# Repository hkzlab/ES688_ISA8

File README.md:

# ES688F / OPL3 8bit ISA Sound Card

## Introduction

This is a sound card for the ISA 8bit bus sporting the **ES688F** chip by *ESS Technology* and the **YMF262** chip by *Yamaha*, also known as the **OPL3**.

This board provides selectable **Sound Blaster PRO** / **Sound Blaster** emulation and **OPL3** compatibility.

It's completely jumper-configurable, requiring no software except the *essvol* utility to set the volume.

This board provides the following connections:

* Speaker out (amplified)
* Line out
* Line in
* Aux in (internal header)
* Microphone in (internal header)
* Joystick port
* MIDI on Joystick port
* Volume regulation pot

### Disclaimer

I take NO responsibility for what happens if you decide to build and use this card. Your computer might crash, catch fire or be destroyed in other nasty ways.
You're encourauged to take what you deem fit from this, and use it in your projects!

### Functionalities

✅ means I tested the functionality and it works, ❌ means I tested the functionality and found issues, ? means that the functionality has yet to be tested.

* [✅] FM Synthesis via OPL3
* [✅] Digital audio playback
* [?] Stereo (left/right channel) check
* [✅] Joystick port
* [✅] Speaker Out (amplified)
* [✅] Line out
* [✅] Line in
* [?] AUX In
* [?] Microphone in
* [✅] MIDI output via Joystick port

The card was tested on:

* [✅] NEC V20 9.5Mhz / DOS 6.22
* [✅] SUNTAC 286 12Mhz motherboard / DOS 6.22

## Configuration

This card is configured via jumpers.

* **JP1**: Selects the **Sound Blaster emulation mode**
  * 1-2: Sound Blaster (DSP v2.11)
  * 2-3 Sound Blaster PRO (DSP v3.1)
  
The following jumpers must me insalled vertically in the block. **1** means **Jumper Present**, **0** means **Jumper Absent**.

* **J2**: Selects the IRQ:
  * 00: IRQ2
  * 10: IRQ5 (default)
  * 01: IRQ7
  * 11: IRQ3
* **J3**: Selects the I/O address:
  * 00: 220h (default)
  * 10: 230h
  * 01: 240h
  * 11: 250h
* **J4**: Selects the DMA channel
  * 00: None
  * 10: DMA2
  * 01: DMA1 (default)
  * 11: DMA3
  
  **WARNING**: /DACK2 and DRQ2 lines are disconnected and must be jumpered on the backside of the board if used, by bridging JP3 and JP2.

## Bill of Materials

**TODO**

## Known Issues

### Rev 1.1

* Missing silkscreen to describe JP1

### Rev 1.0

* Wrong footprints for YAC512 and YMF262 chips
* Volume pot placed after audio decoupling. Wrong.

## Credits

Thanks to [Sergey Kiselev](https://github.com/skiselev) for his symbol/footprint library!

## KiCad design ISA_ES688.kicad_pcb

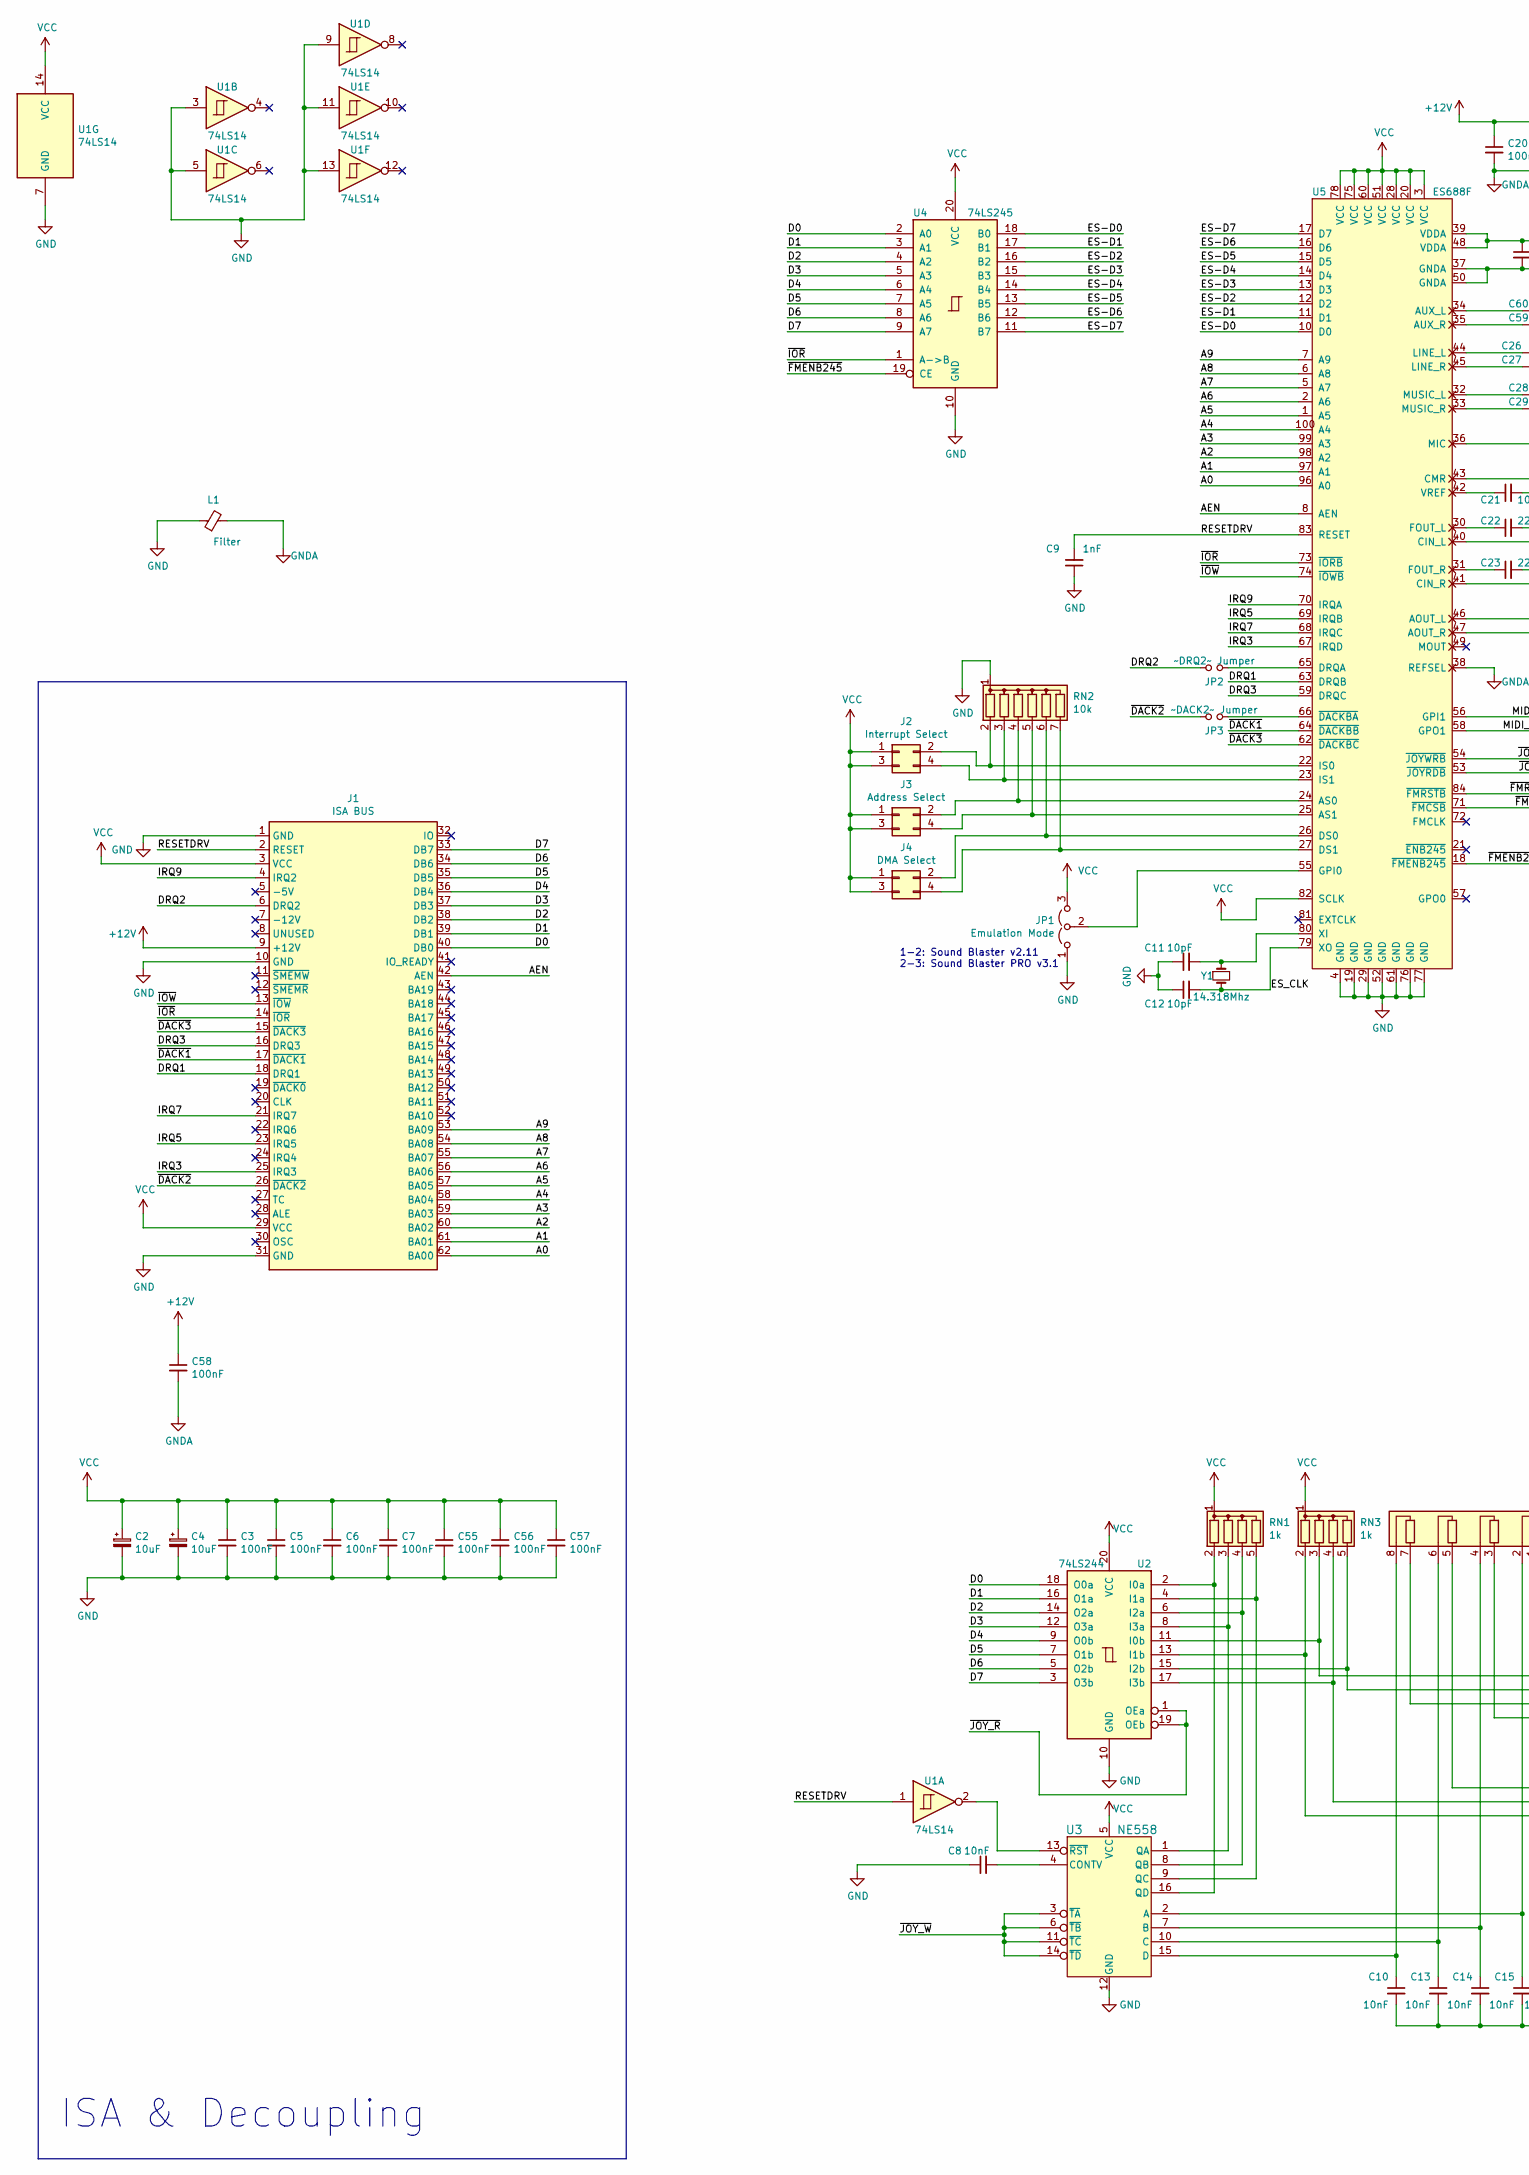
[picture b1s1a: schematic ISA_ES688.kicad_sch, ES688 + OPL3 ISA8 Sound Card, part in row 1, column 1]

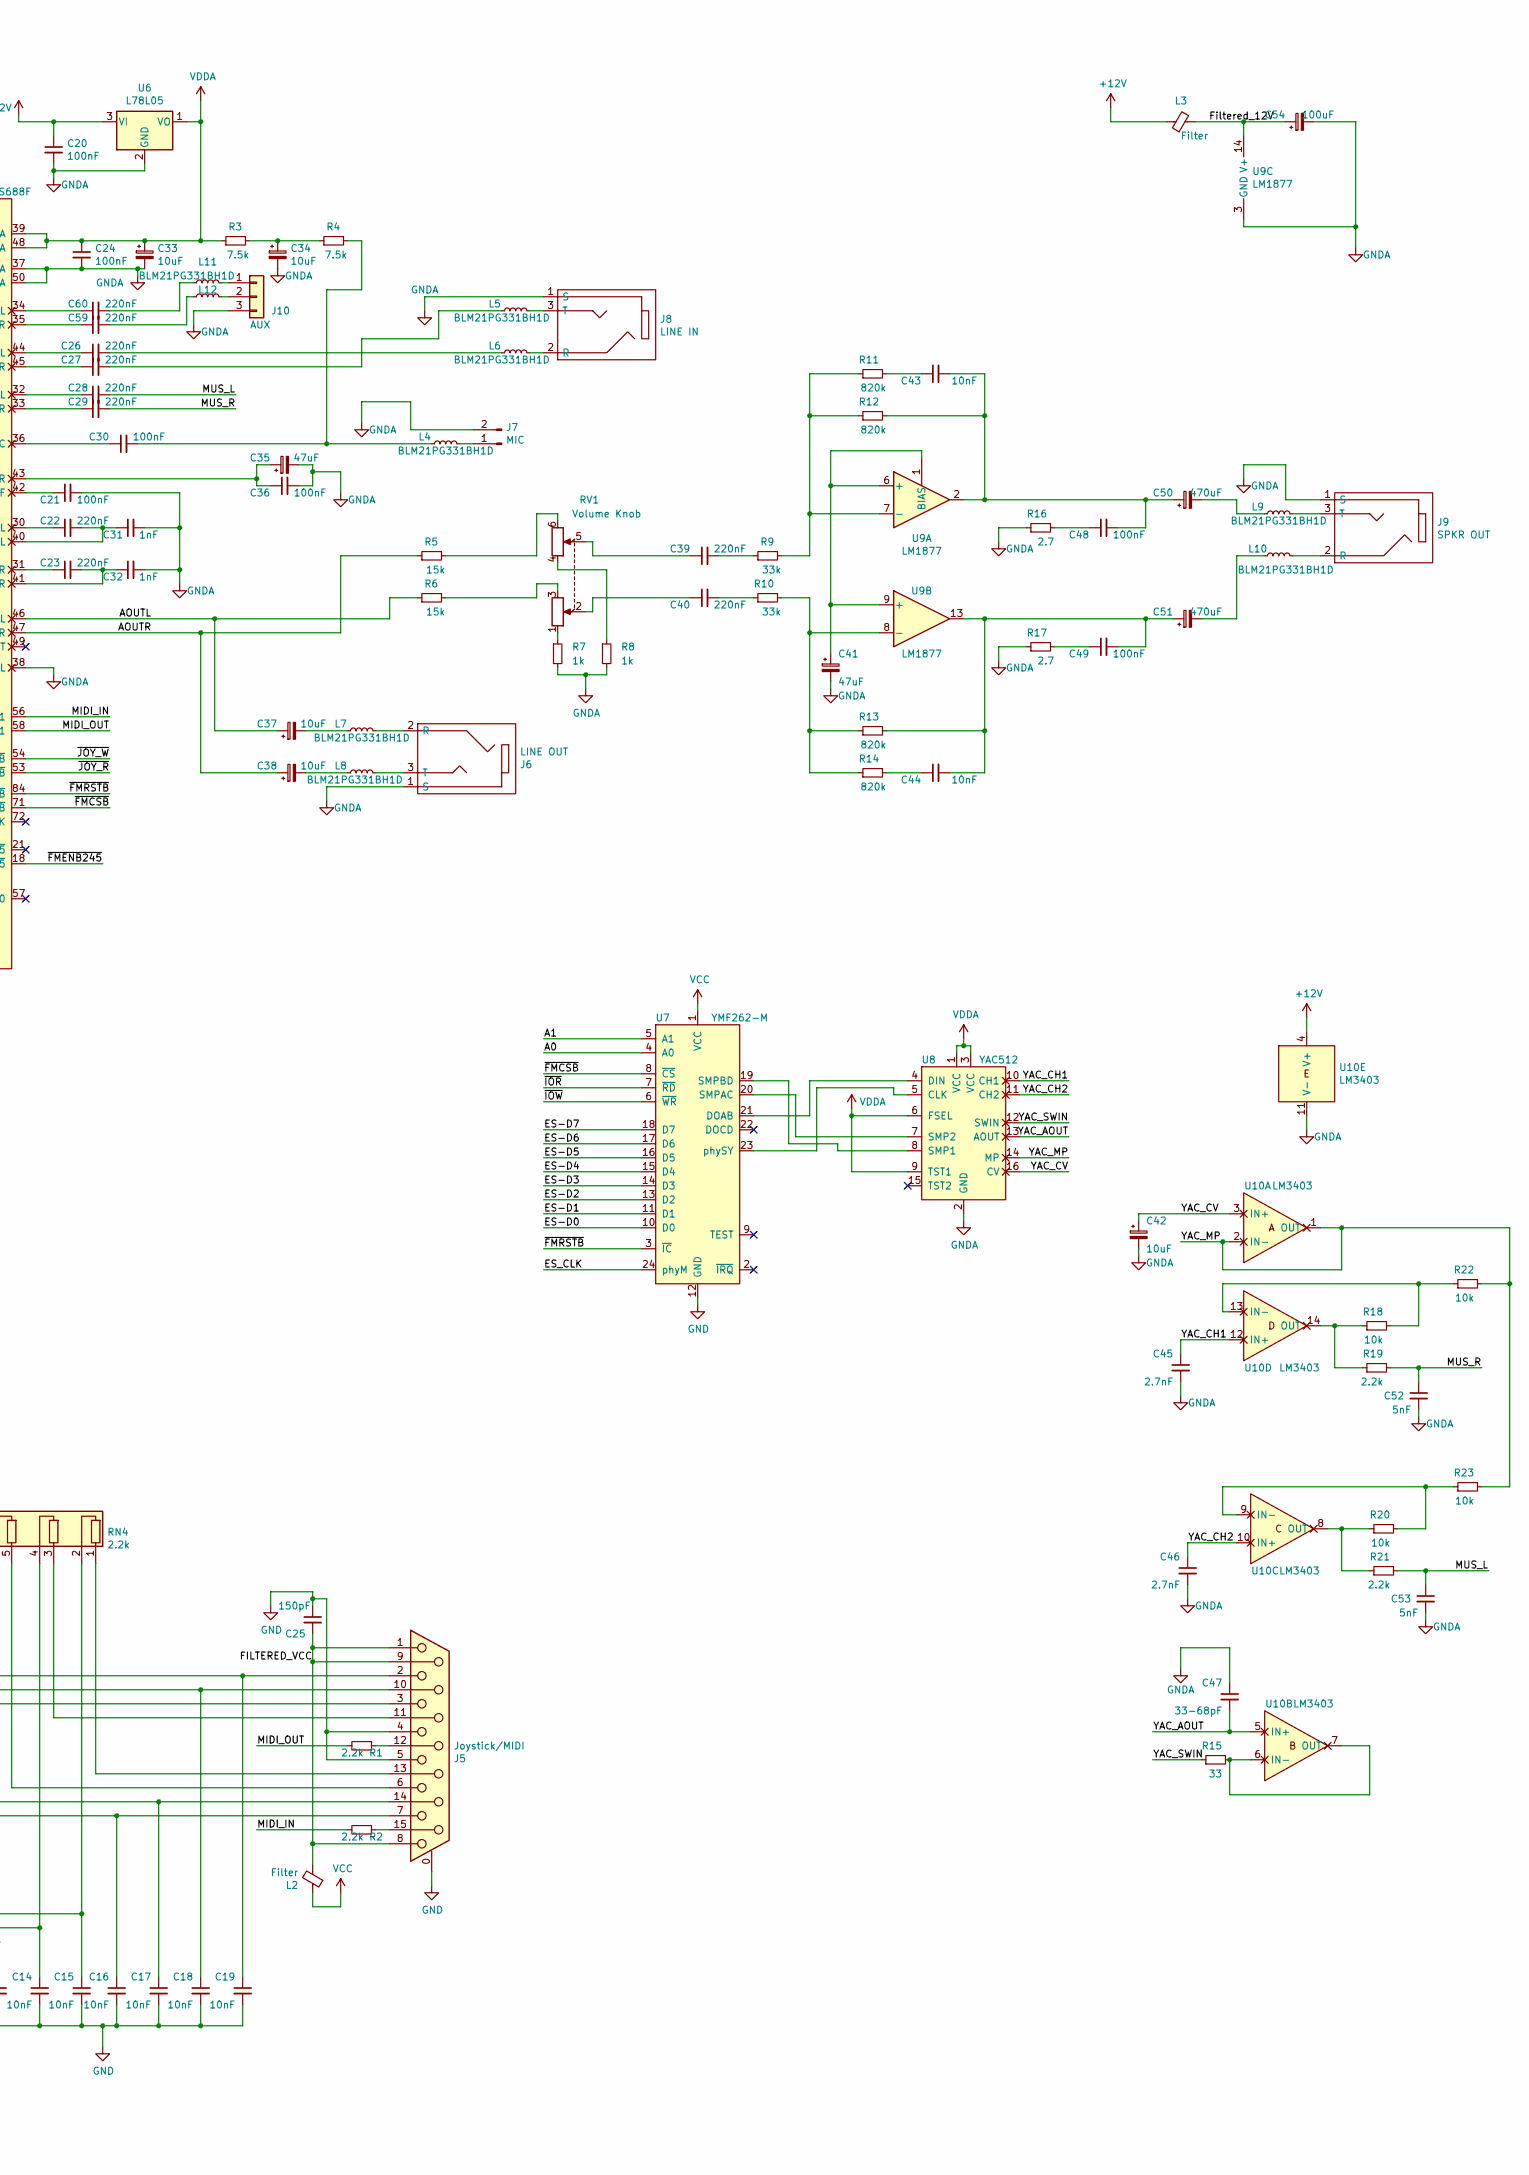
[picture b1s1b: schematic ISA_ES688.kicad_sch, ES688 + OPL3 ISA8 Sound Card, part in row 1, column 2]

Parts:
C2, C4, C33, C34, C37, C38, C42: 10uF; CP_Radial_D5.0mm_P2.50mm
C3, C20, C21, C24, C30, C36, C48, C49, C55, C56, C57, C58: 100nF; C_1206_3216Metric_Pad1.33x1.80mm_HandSolder
C5, C6, C7: 100nF; C_Disc_D5.0mm_W2.5mm_P5.00mm
C8, C10, C13, C14, C15, C16, C17, C18, C19: 10nF; C_Disc_D5.0mm_W2.5mm_P5.00mm
C9, C31, C32: 1nF; C_1206_3216Metric_Pad1.33x1.80mm_HandSolder
C11, C12: 10pF; C_1206_3216Metric_Pad1.33x1.80mm_HandSolder
C22, C23, C26, C27, C28, C29, C39, C40, C59, C60: 220nF; C_1206_3216Metric_Pad1.33x1.80mm_HandSolder
C25: 150pF; C_Disc_D5.0mm_W2.5mm_P5.00mm
C35, C41: 47uF; CP_Radial_D5.0mm_P2.50mm
C43, C44: 10nF; C_1206_3216Metric_Pad1.33x1.80mm_HandSolder
C45, C46: 2.7nF; C_1206_3216Metric_Pad1.33x1.80mm_HandSolder
C47: 33-68pF; C_1206_3216Metric_Pad1.33x1.80mm_HandSolder
C50, C51: 470uF; CP_Radial_D8.0mm_P3.50mm
C52, C53: 5nF; C_1206_3216Metric_Pad1.33x1.80mm_HandSolder
C54: 100uF; CP_Radial_D5.0mm_P2.50mm
J1: ISA BUS; Conn_Edge_PCB_ISA8
J2: Interrupt Select; PinHeader_2x02_P2.54mm_Vertical
J3: Address Select; PinHeader_2x02_P2.54mm_Vertical
J4: DMA Select; PinHeader_2x02_P2.54mm_Vertical
J5: Joystick/MIDI; SB_DB15_152-3415
J6: LINE OUT; Conn_Audio_3.5mm_Stereo_SJ1-352XNG
J7: MIC; PinHeader_1x02_P2.54mm_Vertical
J8: LINE IN; Conn_Audio_3.5mm_Stereo_SJ1-352XNG
J9: SPKR OUT; Conn_Audio_3.5mm_Stereo_SJ1-352XNG
J10: AUX; PinHeader_1x03_P2.54mm_Vertical
JP1: Emulation Mode; PinHeader_1x03_P2.54mm_Vertical
JP2: ~DRQ2~ Jumper; SolderJumper-2_P1.3mm_Open_RoundedPad1.0x1.5mm
JP3: ~DACK2~ Jumper; SolderJumper-2_P1.3mm_Open_RoundedPad1.0x1.5mm
L1, L2, L3: Filter; L_Axial_L5.3mm_D2.2mm_P7.62mm_Horizontal_Vishay_IM-1
L4, L5, L6, L7, L8, L9, L10, L11: BLM21PG331BH1D; L_0805_2012Metric_Pad1.15x1.40mm_HandSolder
L12: 742792093; L_0805_2012Metric_Pad1.15x1.40mm_HandSolder
R1, R2, R19, R21: 2.2k; R_1206_3216Metric_Pad1.30x1.75mm_HandSolder
R3, R4: 7.5k; R_1206_3216Metric_Pad1.30x1.75mm_HandSolder
R5, R6: 15k; R_1206_3216Metric_Pad1.30x1.75mm_HandSolder
R7, R8: 1k; R_1206_3216Metric_Pad1.30x1.75mm_HandSolder
R9, R10: 33k; R_1206_3216Metric_Pad1.30x1.75mm_HandSolder
R11, R12, R13, R14: 820k; R_1206_3216Metric_Pad1.30x1.75mm_HandSolder
R15: 33; R_1206_3216Metric_Pad1.30x1.75mm_HandSolder
R16, R17: 2.7; R_1206_3216Metric_Pad1.30x1.75mm_HandSolder
R18, R20, R22, R23: 10k; R_1206_3216Metric_Pad1.30x1.75mm_HandSolder
RN1, RN3: 1k; R_Array_SIP5
RN2: 10k; R_Array_SIP7
RN4: 2.2k; R_Array_SIP8
RV1: Volume Knob; PTD902
U1: 74LS14; SOIC-14_3.9x8.7mm_P1.27mm
U2: 74LS244; DIP-20_W7.62mm
U3: NE558; DIP-16_W7.62mm
U4: 74LS245; DIP-20_W7.62mm
U5: ES688F; LQFP-14x20mm_P0.5mm
U6: L78L05; TO-92_Inline
U7: YMF262-M; SOP-24
U8: YAC512; SOP-16
U9: LM1877; DIP-14_W7.62mm_LongPads
U10: LM3403; DIP-14_W7.62mm
Y1: 14.318Mhz; Crystal_HC49-4H_Vertical

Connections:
+12V: C20.1, C58.1, J1.9 (+12V), L3.1, U6.3 (VI), U10.4 (V+)
/A0: J1.62 (BA00), U5.96 (A0), U7.4 (A0)
/A1: J1.61 (BA01), U5.97 (A1), U7.5 (A1)
/A2: J1.60 (BA02), U5.98 (A2)
/A3: J1.59 (BA03), U5.99 (A3)
/A4: J1.58 (BA04), U5.100 (A4)
/A5: J1.57 (BA05), U5.1 (A5)
/A6: J1.56 (BA06), U5.2 (A6)
/A7: J1.55 (BA07), U5.5 (A7)
/A8: J1.54 (BA08), U5.6 (A8)
/A9: J1.53 (BA09), U5.7 (A9)
/AEN: J1.42 (AEN), U5.8 (AEN)
/AOUTL: C37.1, R6.1, U5.46 (AOUT_L)
/AOUTR: C38.1, R5.1, U5.47 (AOUT_R)
/D0: J1.40 (DB0), U2.18 (O0a), U4.2 (A0)
/D1: J1.39 (DB1), U2.16 (O1a), U4.3 (A1)
/D2: J1.38 (DB2), U2.14 (O2a), U4.4 (A2)
/D3: J1.37 (DB3), U2.12 (O3a), U4.5 (A3)
/D4: J1.36 (DB4), U2.9 (O0b), U4.6 (A4)
/D5: J1.35 (DB5), U2.7 (O1b), U4.7 (A5)
/D6: J1.34 (DB6), U2.5 (O2b), U4.8 (A6)
/D7: J1.33 (DB7), U2.3 (O3b), U4.9 (A7)
/DRQ1: J1.18 (DRQ1), U5.63 (DRQB)
/DRQ2: J1.6 (DRQ2), JP2.1
/DRQ3: J1.16 (DRQ3), U5.59 (DRQC)
/ES-D0: U4.18 (B0), U5.10 (D0), U7.10 (D0)
/ES-D1: U4.17 (B1), U5.11 (D1), U7.11 (D1)
/ES-D2: U4.16 (B2), U5.12 (D2), U7.13 (D2)
/ES-D3: U4.15 (B3), U5.13 (D3), U7.14 (D3)
/ES-D4: U4.14 (B4), U5.14 (D4), U7.15 (D4)
/ES-D5: U4.13 (B5), U5.15 (D5), U7.16 (D5)
/ES-D6: U4.12 (B6), U5.16 (D6), U7.17 (D6)
/ES-D7: U4.11 (B7), U5.17 (D7), U7.18 (D7)
/ES_CLK: C12.2, U5.79 (XO), U7.24 (phyM), Y1.2
/FILTERED_VCC: C25.2, J5.1, J5.8, J5.9, L2.2
/Filtered_12V: C54.1, L3.2, U9.14 (V+)
/IRQ3: J1.25 (IRQ3), U5.67 (IRQD)
/IRQ5: J1.23 (IRQ5), U5.69 (IRQB)
/IRQ7: J1.21 (IRQ7), U5.68 (IRQC)
/IRQ9: J1.4 (IRQ2), U5.70 (IRQA)
/MIDI_IN: R2.2, U5.56 (GPI1)
/MIDI_OUT: R1.2, U5.58 (GPO1)
/MUS_L: C28.2, C53.1, R21.2
/MUS_R: C29.2, C52.1, R19.2
/RESETDRV: C9.2, J1.2 (RESET), U1.1, U5.83 (RESET)
/YAC_AOUT: C47.2, U8.13 (AOUT), U10.5 (IN+)
/YAC_CH1: C45.1, U8.10 (CH1), U10.12 (IN+)
/YAC_CH2: C46.1, U8.11 (CH2), U10.10 (IN+)
/YAC_CV: C42.1, U8.16 (CV), U10.3 (IN+)
/YAC_MP: R22.2, R23.2, U8.14 (MP), U10.1 (OUT), U10.2 (IN-)
/YAC_SWIN: R15.1, U8.12 (SWIN)
/~DACK1: J1.17 (~DACK1), U5.64 (~DACKBB)
/~DACK2: J1.26 (~DACK2), JP3.1
/~DACK3: J1.15 (~DACK3), U5.62 (~DACKBC)
/~FMCSB: U5.71 (~FMCSB), U7.8 (~CS)
/~FMENB245: U4.19 (CE), U5.18 (~FMENB245)
/~FMRSTB: U5.84 (~FMRSTB), U7.3 (~IC)
/~IOR: J1.14 (~IOR), U4.1 (A->B), U5.73 (~IORB), U7.7 (~RD)
/~IOW: J1.13 (~IOW), U5.74 (~IOWB), U7.6 (~WR)
/~JOY_R: U2.1 (OEa), U2.19 (OEb), U5.53 (~JOYRDB)
/~JOY_W: U3.3 (~TA), U3.6 (~TB), U3.11 (~TC), U3.14 (~TD), U5.54 (~JOYWRB)
GND: C2.2, C3.2, C4.2, C5.2, C6.2, C7.2, C8.1, C9.1, C10.2, C11.1, C12.1, C13.2, C14.2, C15.2, C16.2, C17.2, C18.2, C19.2, C25.1, C55.2, C56.2, C57.2, J1.1 (GND), J1.10 (GND), J1.31 (GND), J5.0 (PAD), J5.4, J5.5, JP1.1 (A), L1.1, RN2.1 (common), U1.3, U1.5, U1.7 (GND), U1.9, U1.11, U1.13, U2.10 (GND), U3.12 (GND), U4.10 (GND), U5.4 (GND), U5.19 (GND), U5.29 (GND), U5.52 (GND), U5.61 (GND), U5.76 (GND), U5.77 (GND), U7.12 (GND)
GNDA: C20.2, C21.2, C24.2, C31.2, C32.2, C33.2, C34.2, C35.2, C36.2, C41.2, C42.2, C45.2, C46.2, C47.1, C52.2, C53.2, C54.2, C58.2, J6.1 (S), J7.2, J8.1 (S), J9.1 (S), J10.3, L1.2, R7.2, R8.2, R16.1, R17.1, U5.37 (GNDA), U5.38 (REFSEL), U5.50 (GNDA), U6.2 (GND), U8.2 (GND), U9.3 (GND), U9.4 (GND), U9.5 (GND), U9.10 (GND), U9.11 (GND), U9.12 (GND), U10.11 (V-); also elsewhere on the board
unnamed: C8.2, U3.4 (CONTV)
unnamed: C10.1, RN4.8 (R4.2), U3.15 (D)
unnamed: C11.2, U5.80 (XI), Y1.1
unnamed: C13.1, RN4.6 (R3.2), U3.10 (C)
unnamed: C14.1, RN4.4 (R2.2), U3.7 (B)
unnamed: C15.1, RN4.2 (R1.2), U3.2 (A)
unnamed: C16.1, J5.7, RN3.2 (R1), U2.13 (I1b)
unnamed: C17.1, J5.14, RN3.4 (R3), U2.17 (I3b)
unnamed: C18.1, J5.10, RN3.5 (R4), U2.15 (I2b)
unnamed: C19.1, J5.2, RN3.3 (R2), U2.11 (I0b)
unnamed: C21.1, U5.42 (VREF)
unnamed: C22.1, U5.30 (FOUT_L)
unnamed: C22.2, C31.1, U5.40 (CIN_L)
unnamed: C23.1, U5.31 (FOUT_R)
unnamed: C23.2, C32.1, U5.41 (CIN_R)
unnamed: C26.1, U5.44 (LINE_L)
unnamed: C26.2, L6.1
unnamed: C27.1, U5.45 (LINE_R)
unnamed: C27.2, L5.1
unnamed: C28.1, U5.32 (MUSIC_L)
unnamed: C29.1, U5.33 (MUSIC_R)
unnamed: C30.1, U5.36 (MIC)
unnamed: C30.2, L4.1, R4.2
unnamed: C34.1, R3.2, R4.1
unnamed: C35.1, C36.1, U5.43 (CMR)
unnamed: C37.2, L7.1
unnamed: C38.2, L8.1
unnamed: C39.2, R9.1
unnamed: C40.2, R10.1
unnamed: C41.1, U9.1 (BIAS), U9.6 (+), U9.9 (+)
unnamed: C43.1, R11.2
unnamed: C43.2, C48.2, C50.1, R12.2, U9.2
unnamed: C44.1, R14.2
unnamed: C44.2, C49.2, C51.1, R13.2, U9.13
unnamed: C48.1, R16.2
unnamed: C49.1, R17.2
unnamed: C50.2, L9.1
unnamed: C51.2, L10.1
unnamed: C59.1, U5.35 (AUX_R)
unnamed: C59.2, L12.1
unnamed: C60.1, U5.34 (AUX_L)
unnamed: C60.2, L11.1
unnamed: J2.2, RN2.2 (R1), U5.22 (IS0)
unnamed: J2.4, RN2.3 (R2), U5.23 (IS1)
unnamed: J3.2, RN2.4 (R3), U5.24 (AS0)
unnamed: J3.4, RN2.5 (R4), U5.25 (AS1)
unnamed: J4.2, RN2.6 (R5), U5.26 (DS0)
unnamed: J4.4, RN2.7 (R6), U5.27 (DS1)
unnamed: J5.3, RN4.7 (R4.1)
unnamed: J5.6, RN4.5 (R3.1)
unnamed: J5.11 (P111), RN4.3 (R2.1)
unnamed: J5.12, R1.1
unnamed: J5.13, RN4.1 (R1.1)
unnamed: J5.15, R2.1
unnamed: J6.2 (R), L7.2
unnamed: J6.3 (T), L8.2
unnamed: J7.1, L4.2
unnamed: J8.2 (R), L6.2
unnamed: J8.3 (T), L5.2
unnamed: J9.2 (R), L10.2
unnamed: J9.3 (T), L9.2
unnamed: J10.1, L11.2
unnamed: J10.2, L12.2
unnamed: JP1.2 (C), U5.55 (GPI0)
unnamed: JP2.2, U5.65 (DRQA)
unnamed: JP3.2, U5.66 (~DACKBA)
unnamed: R5.2, RV1.6
unnamed: R6.2, RV1.3
unnamed: R10.2, R13.1, R14.1, U9.8 (-)
unnamed: R9.2, R11.1, R12.1, U9.7 (-)
unnamed: R15.2, U10.6 (IN-), U10.7 (OUT)
unnamed: R18.1, R19.1, U10.14 (OUT)
unnamed: R18.2, R22.1, U10.13 (IN-)
unnamed: R20.1, R21.1, U10.8 (OUT)
unnamed: R20.2, R23.1, U10.9 (IN-)
unnamed: RN1.2 (R1), U2.2 (I0a), U3.16 (QD)
unnamed: RN1.3 (R2), U2.8 (I3a), U3.1 (QA)
unnamed: RN1.4 (R3), U2.6 (I2a), U3.8 (QB)
unnamed: RN1.5 (R4), U2.4 (I1a), U3.9 (QC)
unnamed: U1.2, U3.13 (~RST)
unnamed: U7.19 (SMPBD), U8.8 (SMP1)
unnamed: U7.20 (SMPAC), U8.7 (SMP2)
unnamed: U7.21 (DOAB), U8.4 (DIN)
unnamed: U7.23 (phySY), U8.5 (CLK)
VCC: C2.1, C3.1, C4.1, C5.1, C6.1, C7.1, C55.1, C56.1, C57.1, J1.3 (VCC), J1.29 (VCC), J2.1, J2.3, J3.1, J3.3, J4.1, J4.3, JP1.3 (B), L2.1, RN1.1 (common), RN3.1 (common), U1.14 (VCC), U2.20 (VCC), U3.5 (VCC), U4.20 (VCC), U5.3 (VCC), U5.20 (VCC), U5.28 (VCC), U5.51 (VCC), U5.60 (VCC), U5.75 (VCC), U5.78 (VCC), U5.82 (SCLK), U7.1 (VCC)
VDDA: C24.1, C33.1, R3.1, U5.39 (VDDA), U5.48 (VDDA), U6.1 (VO), U8.1 (VCC), U8.3 (VCC), U8.6 (FSEL), U8.9 (TST1)

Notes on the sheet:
ISA & Decoupling
1-2: Sound Blaster v2.11 2-3: Sound Blaster PRO v3.1

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
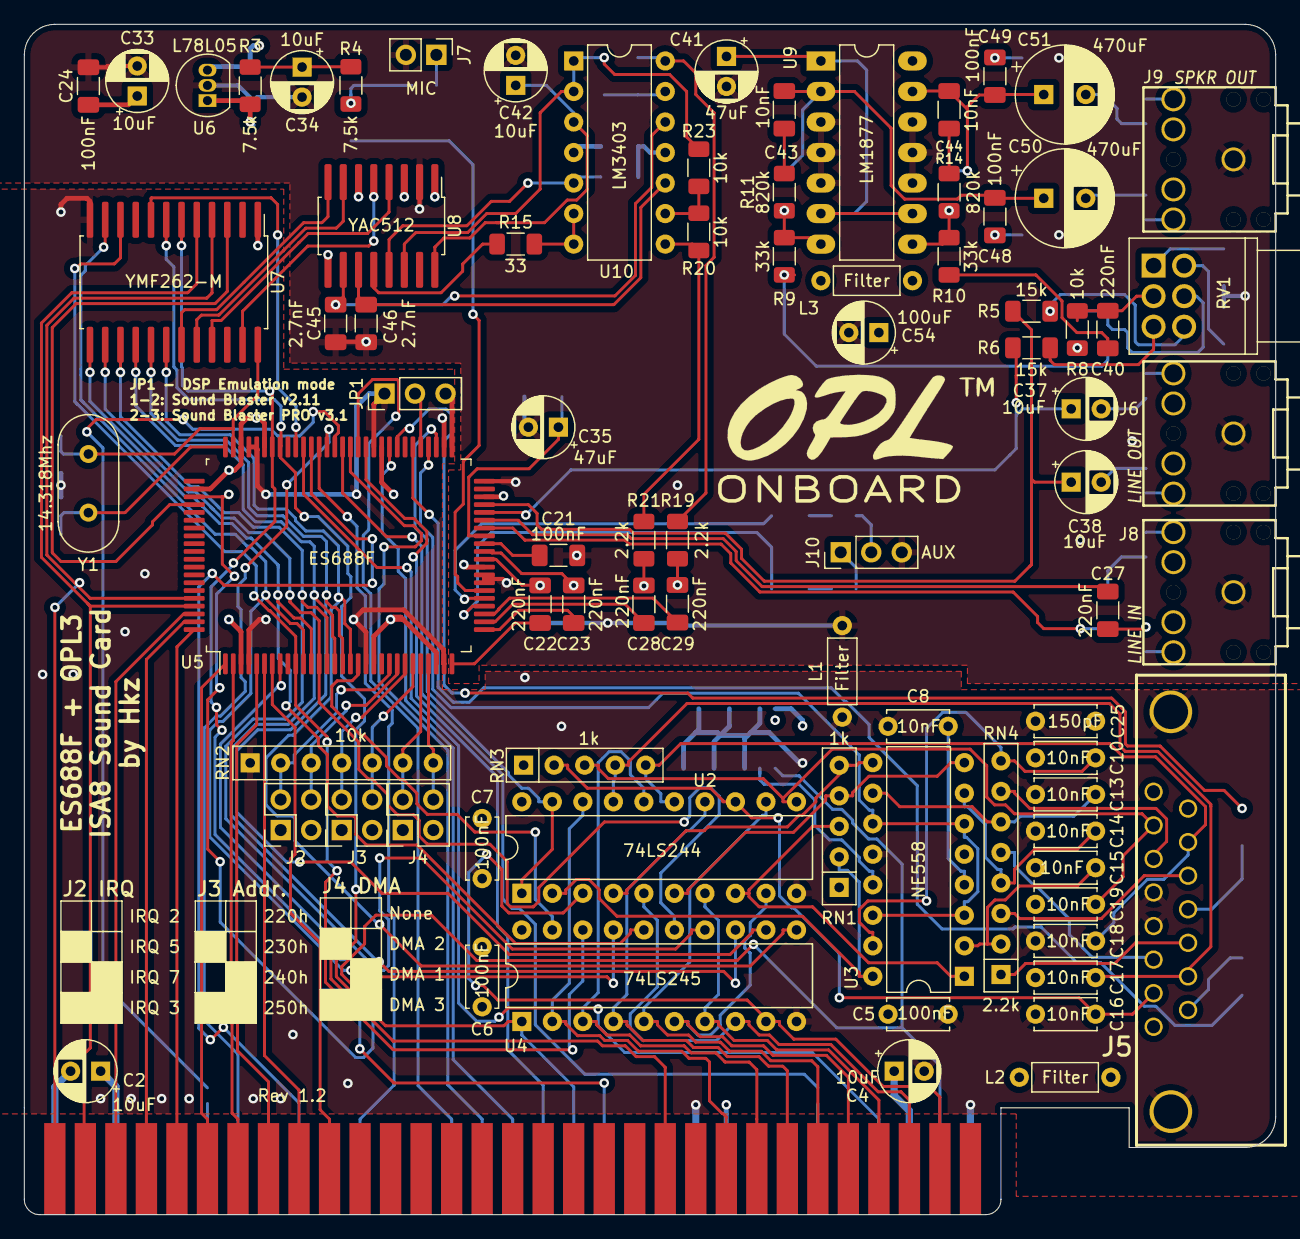
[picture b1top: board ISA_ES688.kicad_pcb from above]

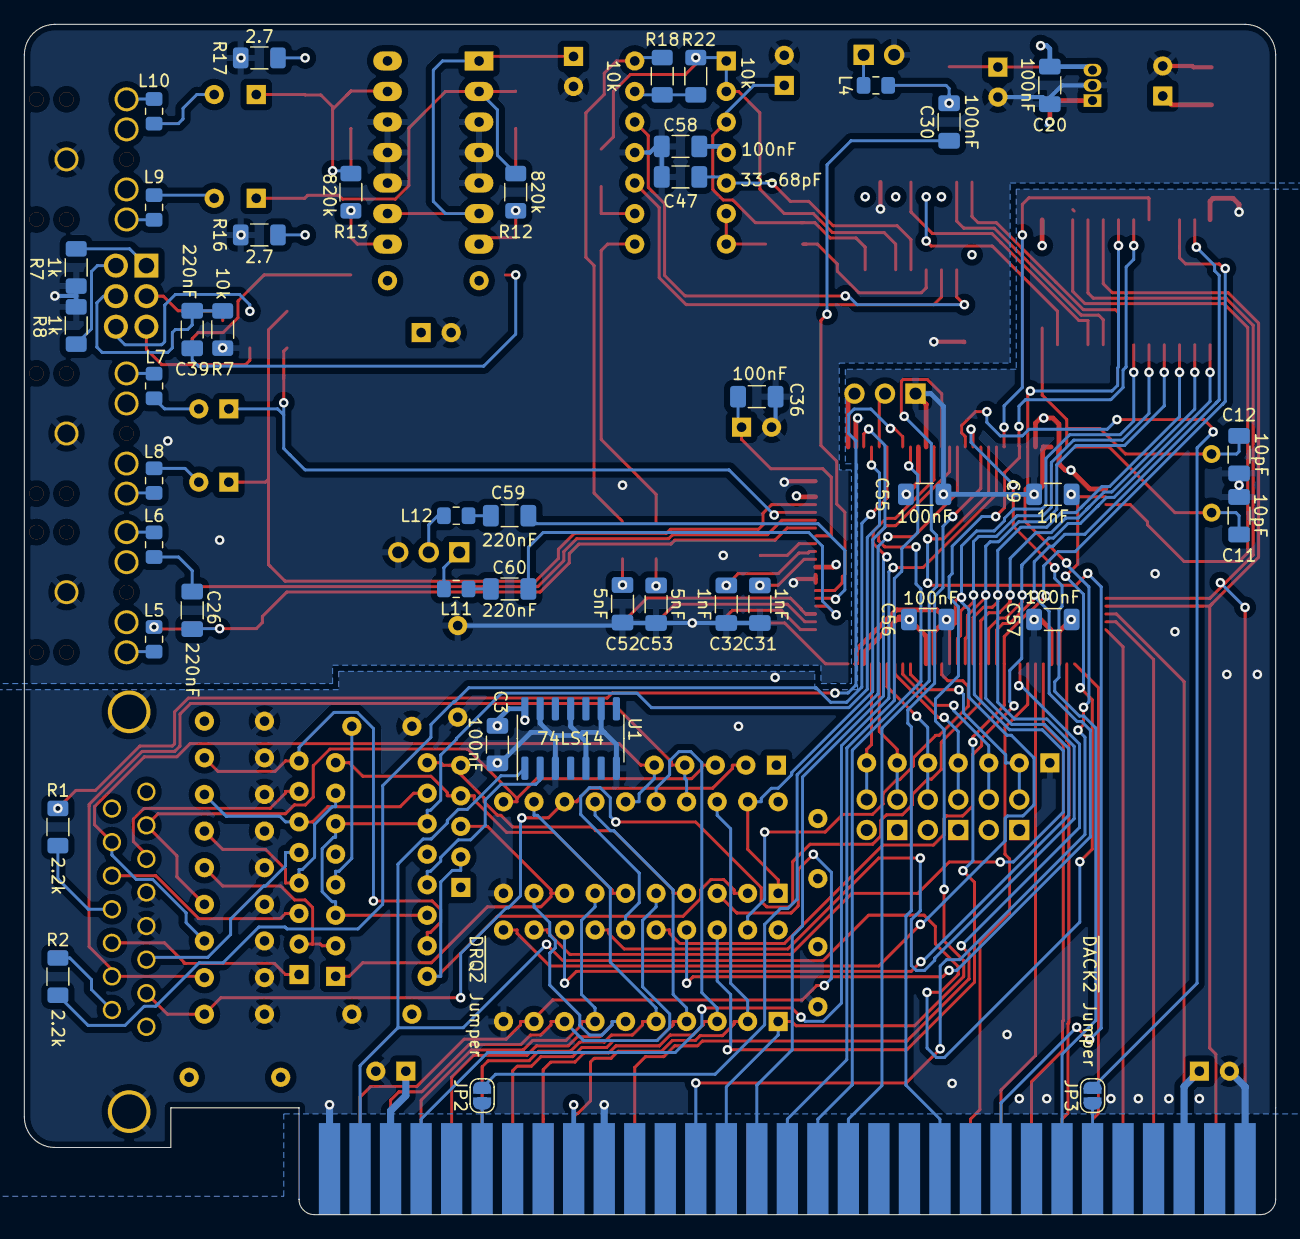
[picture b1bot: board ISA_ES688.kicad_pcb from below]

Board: 4 copper layers, 104.1 x 99.1 mm, 125 parts (43 on the bottom side), 153 nets.

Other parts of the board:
R7#2, R8#2: 1k; R_1206_3216Metric_Pad1.30x1.75mm_HandSolder

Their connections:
GNDA: R7#2.2, R8#2.2; also elsewhere on the board

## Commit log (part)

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2021-05-13 Begin creating the ES866F symbol
2021-05-13 Pin changes for ES688
2021-05-13 Add correct docs for project
2021-05-13 Edit the ES688F symbol
2021-05-13 ES688F symbol
2021-05-13 Done symbol for ES688F
2021-05-13 Begin creating symbol for OPL3
2021-05-13 added YMF262-M
2021-05-13 pins for YAC512
2021-05-13 YAC512
2021-05-13 Add LN3403
2021-05-13 Add amplifier doc
2021-05-14 Add NE558 symbol
2021-05-14 Begin changing the schematics
2021-05-14 Remove some unused components
2021-05-14 Complete more schematic
2021-05-14 Cleanup for joystick part
2021-05-14 More joystick schematics
2021-05-14 Add gnd connection to caps for joystick
2021-05-14 Add VDDA symbol
2021-05-14 Replace resistor network
2021-05-15 Add more components to schematic
2021-05-15 Start wiring the OPL3 to the ES688 chip
2021-05-15 Connect OPL3 to YAC512
2021-05-15 Begin reversing opamp schematic
2021-05-15 Implement part of OPAMP circuit
2021-05-15 Mark more pins as not connected
2021-05-15 Rewire midi connection
2021-05-15 Reorganize connections a bit
2021-05-16 More OP-AMP circuit
2021-05-16 Completed OPAMP circuit?
2021-05-16 Add volume pot footprint, and volume control to sch
2021-05-17 Begin assigning footprints
2021-05-17 Assign more footprints
2021-05-17 Finished assigning footprints
2021-05-18 Begin laying out parts
2021-05-18 Begin placing some components on the board
2021-05-18 More placing on PCB
2021-05-18 More placements
2021-05-18 More movement on PCB
2021-05-18 Additional trace routing
2021-05-18 Placed all components on PCB
2021-05-18 More routing for audio part
2021-05-18 More routing
2021-05-18 Routed audio section
2021-05-18 Completed routing of board
2021-05-18 Added descriptions to silkscreen
2021-05-18 Another silkscreen fix
2021-05-18 Updated footprint size
2021-05-19 Slightly reroute a trace
2021-05-19 Refill zones
2021-05-19 Added two resistors after the volume pot
2021-05-20 Fix some traces in gnd plane
2021-05-23 Moved some connectors and change DB15 footprint
2021-05-24 Add keystone bracket
2021-05-25 Move components to use the keystone 9200-3 bracket
2021-05-25 Change spacing in jumper's silkscreen
2021-05-26 Replaced two ceramics caps with electrolitics
2021-05-26 Heavier 12V trace
2021-05-26 More ground plane!
2021-06-07 Fix component symbol
2021-06-12 Move connectors slightly forward
2021-06-12 Rerouted some traces
2021-06-16 Changed silkscreen for IRQ
2021-06-16 Fattened some tracks
2021-06-16 Fixed some more silkscreen
2021-06-16 Add gerbers for rev 1.0
2021-06-17 Fixed AEN pin name
2021-07-01 Add new footprints for SOP16 and 24
2021-07-01 Redraw part of the PCB to conform to new footprints
2021-07-01 Fix silkscreen
2021-07-01 Another fix to silkscreen
2021-07-02 Updated silkscreen and version on schematic
2021-07-02 Reroute some traces
2021-07-03 Change configuration pin description
2021-07-03 Add OPL logo
2021-07-03 Change silkscreen
2021-07-03 Further silkscreen changes
2021-07-03 More silkscreen adjustments
2021-07-04 Enlarged footprints for YAC and OPL, again
2021-07-05 Another small silkscreen fix
2021-07-07 Add note in schematic
2021-07-07 Moved the potentiometer for volume before decoupling
2021-07-07 Reroute some tracks
2021-07-09 Add headers for aux port
2021-07-10 Add ferrite beads at outputs and inputs
2021-07-11 Update beads used for audio lines
2021-07-19 Changed fixed resistor values for potentiometer
2021-07-19 Fix name in schematic
2021-07-27 Add rev 1.1 gerbers
2021-07-27 Add 1.1 gerbers
2021-08-14 Added silkscreen for JP1
2021-08-15 Move tweak silkscreen
2021-08-16 Begin adding README for ES688 card
2021-08-22 Added some notes to README
2021-08-22 Further notes in README
2021-08-22 Completed some more testing
2021-08-22 More testing
2021-11-09 Update KiCad url
2023-10-13 Initial import to Kicad 7
